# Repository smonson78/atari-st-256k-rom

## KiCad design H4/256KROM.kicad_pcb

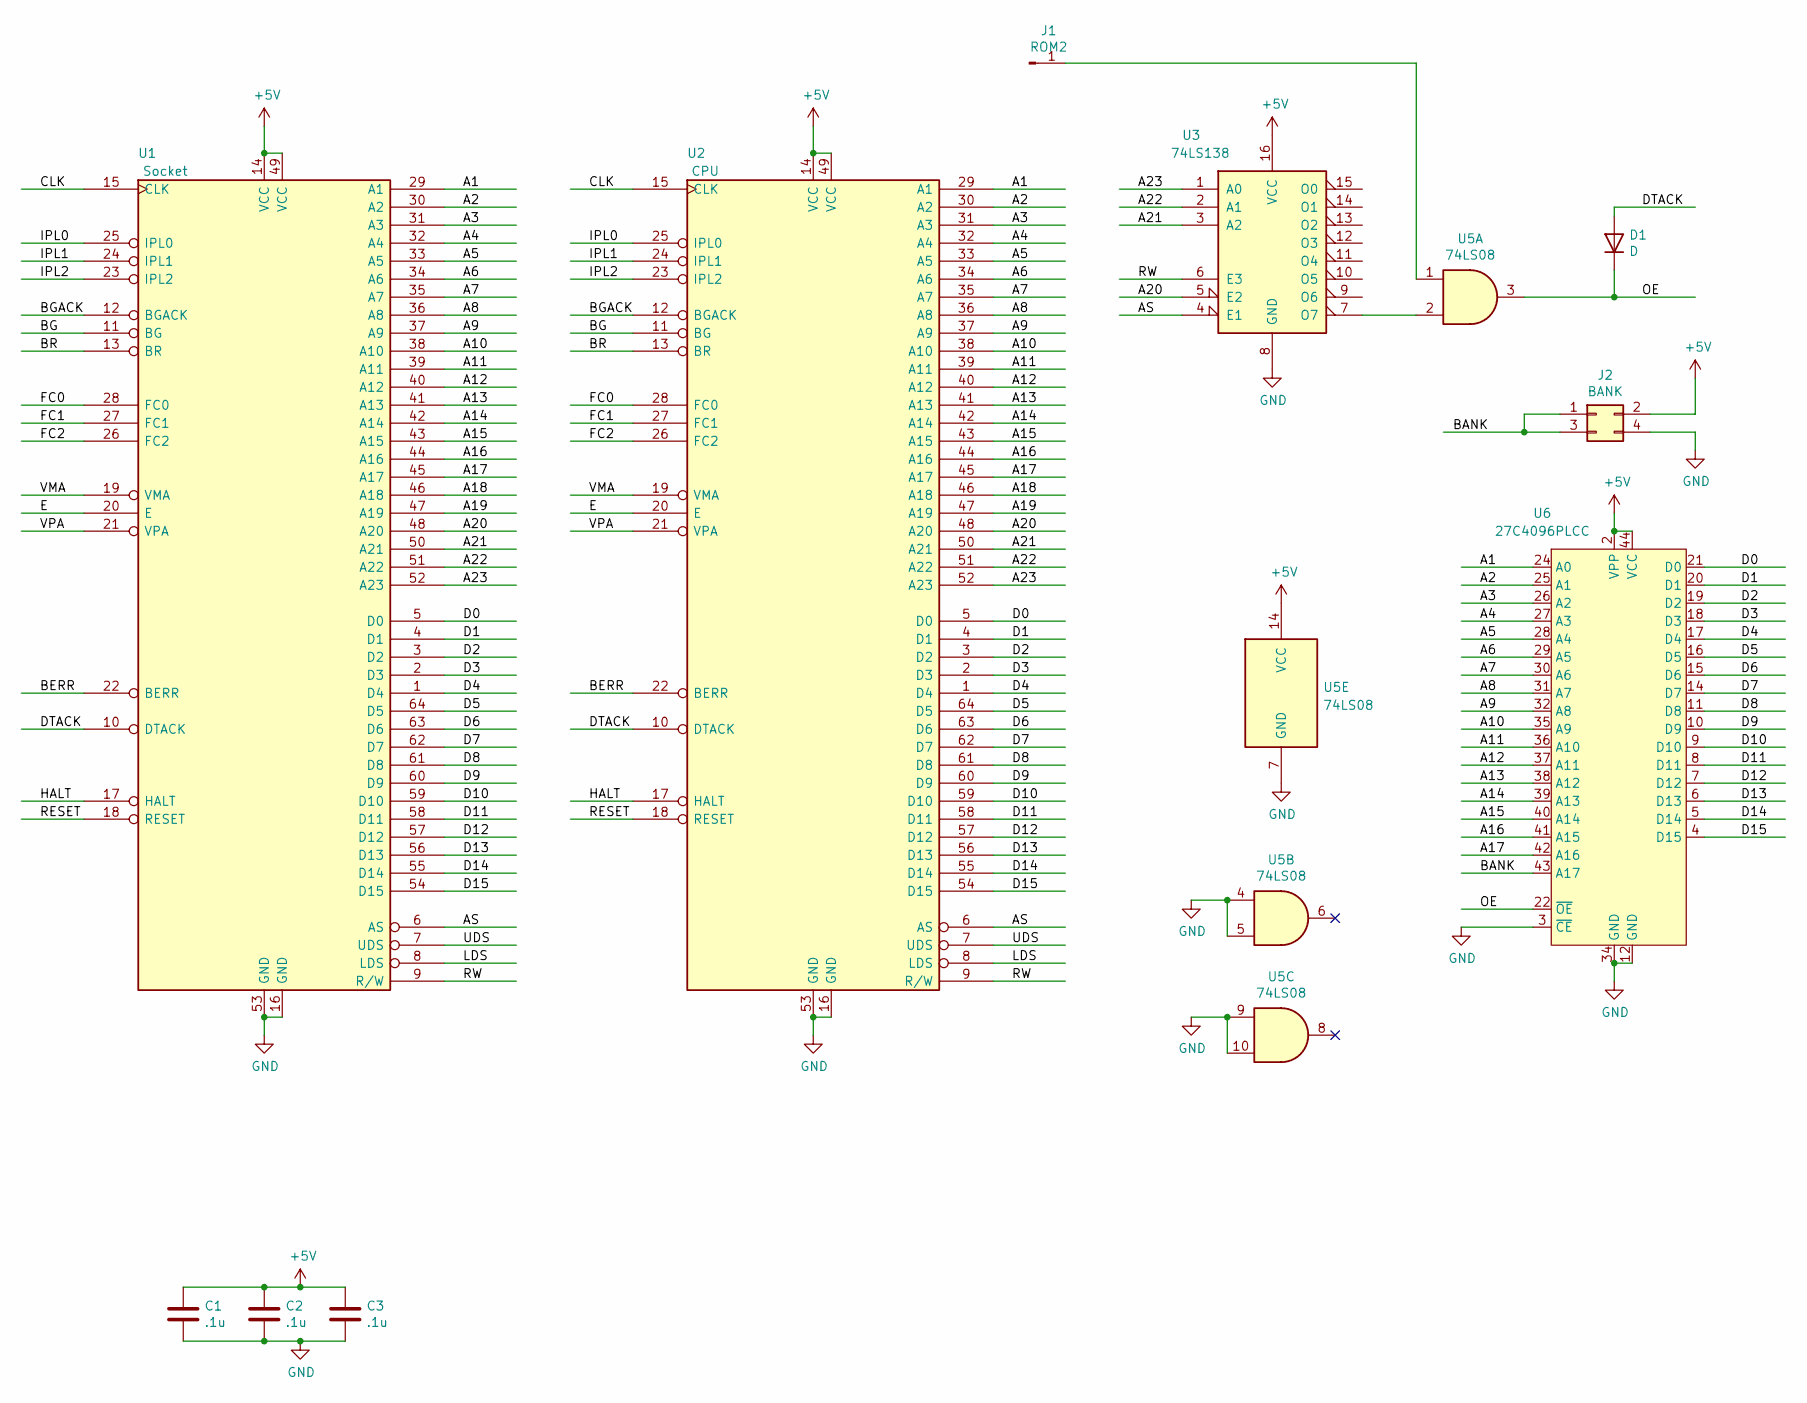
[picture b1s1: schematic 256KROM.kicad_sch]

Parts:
C1, C2, C3: .1u; C_0603_1608Metric
D1: D; D_A-405_P7.62mm_Horizontal
J1: ROM2; PinHeader_1x01_P2.54mm_Horizontal
J2: BANK; PinHeader_2x02_P2.54mm_Vertical
U1: Socket; DIP-64_W22.86mm_LongPads
U2: CPU; DIP-64_W22.86mm_LongPads
U3: 74LS138; SOIC-16_3.9x9.9mm_P1.27mm
U5: 74LS08; SOIC-14_3.9x8.7mm_P1.27mm
U6: 27C4096PLCC; PLCC-44_THT-Socket

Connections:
+5V: C1.1, C2.1, C3.1, J2.2, U1.14 (VCC), U1.49 (VCC), U2.14 (VCC), U2.49 (VCC), U3.16 (VCC), U5.14 (VCC), U6.2 (VPP), U6.44 (VCC)
/A1: U1.29 (A1), U2.29 (A1), U6.24 (A0)
/A2: U1.30 (A2), U2.30 (A2), U6.25 (A1)
/A3: U1.31 (A3), U2.31 (A3), U6.26 (A2)
/A4: U1.32 (A4), U2.32 (A4), U6.27 (A3)
/A5: U1.33 (A5), U2.33 (A5), U6.28 (A4)
/A6: U1.34 (A6), U2.34 (A6), U6.29 (A5)
/A7: U1.35 (A7), U2.35 (A7), U6.30 (A6)
/A8: U1.36 (A8), U2.36 (A8), U6.31 (A7)
/A9: U1.37 (A9), U2.37 (A9), U6.32 (A8)
/A10: U1.38 (A10), U2.38 (A10), U6.35 (A9)
/A11: U1.39 (A11), U2.39 (A11), U6.36 (A10)
/A12: U1.40 (A12), U2.40 (A12), U6.37 (A11)
/A13: U1.41 (A13), U2.41 (A13), U6.38 (A12)
/A14: U1.42 (A14), U2.42 (A14), U6.39 (A13)
/A15: U1.43 (A15), U2.43 (A15), U6.40 (A14)
/A16: U1.44 (A16), U2.44 (A16), U6.41 (A15)
/A17: U1.45 (A17), U2.45 (A17), U6.42 (A16)
/A18: U1.46 (A18), U2.46 (A18)
/A19: U1.47 (A19), U2.47 (A19)
/A20: U1.48 (A20), U2.48 (A20), U3.5 (E2)
/A21: U1.50 (A21), U2.50 (A21), U3.3 (A2)
/A22: U1.51 (A22), U2.51 (A22), U3.2 (A1)
/A23: U1.52 (A23), U2.52 (A23), U3.1 (A0)
/AS: U1.6 (AS), U2.6 (AS), U3.4 (E1)
/BANK: J2.1, J2.3, U6.43 (A17)
/BERR: U1.22 (BERR), U2.22 (BERR)
/BG: U1.11 (BG), U2.11 (BG)
/BGACK: U1.12 (BGACK), U2.12 (BGACK)
/BR: U1.13 (BR), U2.13 (BR)
/CLK: U1.15 (CLK), U2.15 (CLK)
/D0: U1.5 (D0), U2.5 (D0), U6.21 (D0)
/D1: U1.4 (D1), U2.4 (D1), U6.20 (D1)
/D2: U1.3 (D2), U2.3 (D2), U6.19 (D2)
/D3: U1.2 (D3), U2.2 (D3), U6.18 (D3)
/D4: U1.1 (D4), U2.1 (D4), U6.17 (D4)
/D5: U1.64 (D5), U2.64 (D5), U6.16 (D5)
/D6: U1.63 (D6), U2.63 (D6), U6.15 (D6)
/D7: U1.62 (D7), U2.62 (D7), U6.14 (D7)
/D8: U1.61 (D8), U2.61 (D8), U6.11 (D8)
/D9: U1.60 (D9), U2.60 (D9), U6.10 (D9)
/D10: U1.59 (D10), U2.59 (D10), U6.9 (D10)
/D11: U1.58 (D11), U2.58 (D11), U6.8 (D11)
/D12: U1.57 (D12), U2.57 (D12), U6.7 (D12)
/D13: U1.56 (D13), U2.56 (D13), U6.6 (D13)
/D14: U1.55 (D14), U2.55 (D14), U6.5 (D14)
/D15: U1.54 (D15), U2.54 (D15), U6.4 (D15)
/DTACK: D1.2 (A), U1.10 (DTACK), U2.10 (DTACK)
/E: U1.20 (E), U2.20 (E)
/FC0: U1.28 (FC0), U2.28 (FC0)
/FC1: U1.27 (FC1), U2.27 (FC1)
/FC2: U1.26 (FC2), U2.26 (FC2)
/HALT: U1.17 (HALT), U2.17 (HALT)
/IPL0: U1.25 (IPL0), U2.25 (IPL0)
/IPL1: U1.24 (IPL1), U2.24 (IPL1)
/IPL2: U1.23 (IPL2), U2.23 (IPL2)
/LDS: U1.8 (LDS), U2.8 (LDS)
/OE: D1.1 (K), U5.3, U6.22 (~OE)
/RESET: U1.18 (RESET), U2.18 (RESET)
/RW: U1.9 (R/W), U2.9 (R/W), U3.6 (E3)
/UDS: U1.7 (UDS), U2.7 (UDS)
/VMA: U1.19 (VMA), U2.19 (VMA)
/VPA: U1.21 (VPA), U2.21 (VPA)
GND: C1.2, C2.2, C3.2, J2.4, U1.16 (GND), U1.53 (GND), U2.16 (GND), U2.53 (GND), U3.8 (GND), U5.4, U5.5, U5.7 (GND), U5.9, U5.10, U6.3 (~CE), U6.12 (GND), U6.34 (GND)
unnamed: J1.1, U5.1
unnamed: U3.7 (O7), U5.2

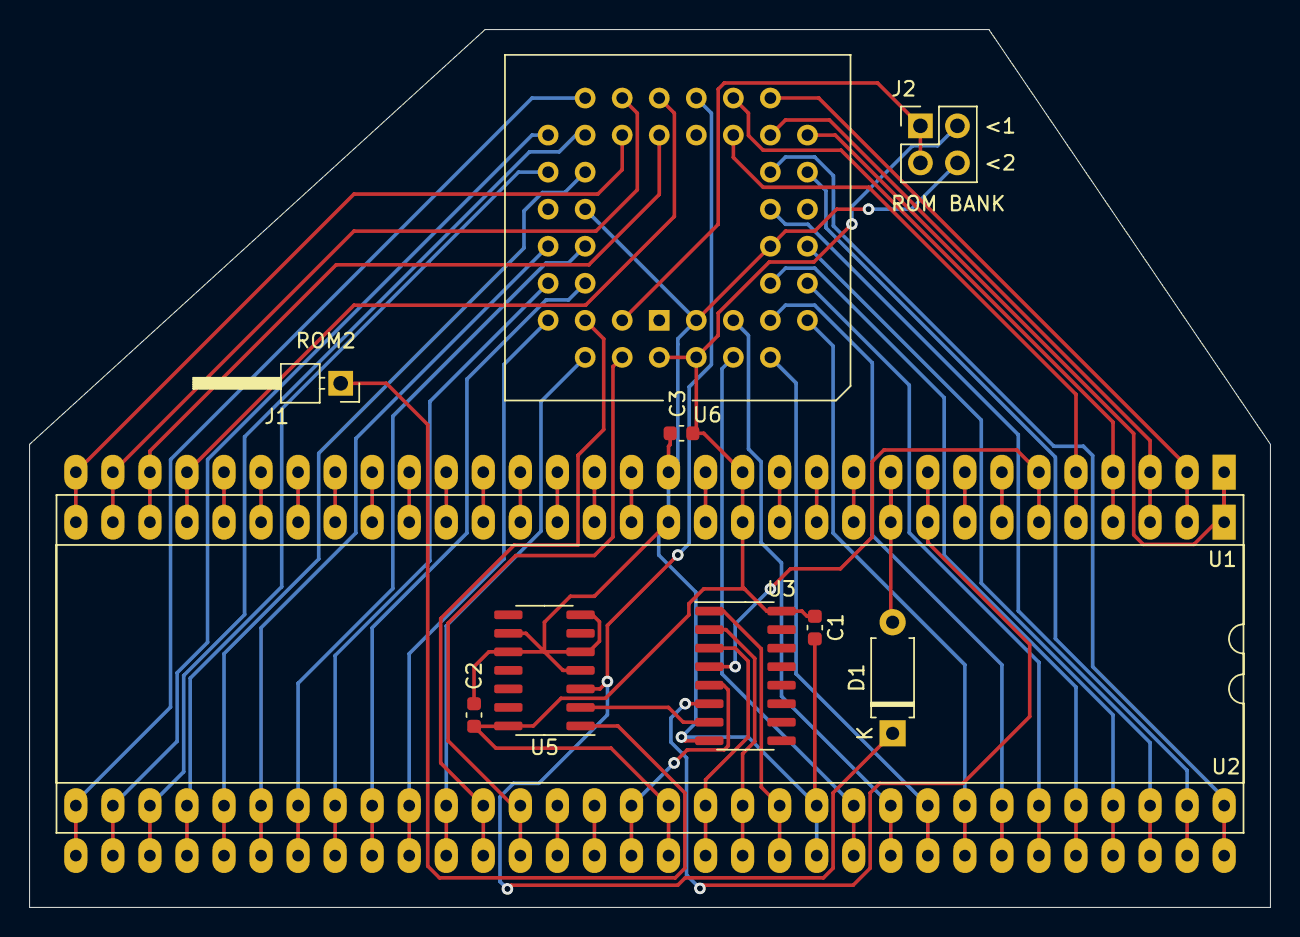
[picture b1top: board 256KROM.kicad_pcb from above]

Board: 2 copper layers, 85.1 x 60.2 mm, 11 parts (0 on the bottom side), 66 nets.

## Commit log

2024-01-14 Added H4 version (working)
